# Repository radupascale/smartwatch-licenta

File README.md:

# Intro

This repository contains all the files necessary to build the smartwatch I developed for my thesis at the Computer Science Faculty of UPB.
I plan to add step-by-step building instructions in the future, but for now I'll leave only an overview of the directory structure.

- board: Schematics and PCB layout
    - fusion: Fusion project archive
    - proto: KiCad prototype project
- CAD
    - 3d-files: .stl files for 3D printing the case
    - components: .STEP files for some components
- src: platform.io project files and deps

# Building

```bash
git clone --recurse-submodules git@github.com:radupascale/smartwatch-licenta.git
```

Afterwards open the `src` directory and build&upload using `platformio` (this project used the VScode extension).

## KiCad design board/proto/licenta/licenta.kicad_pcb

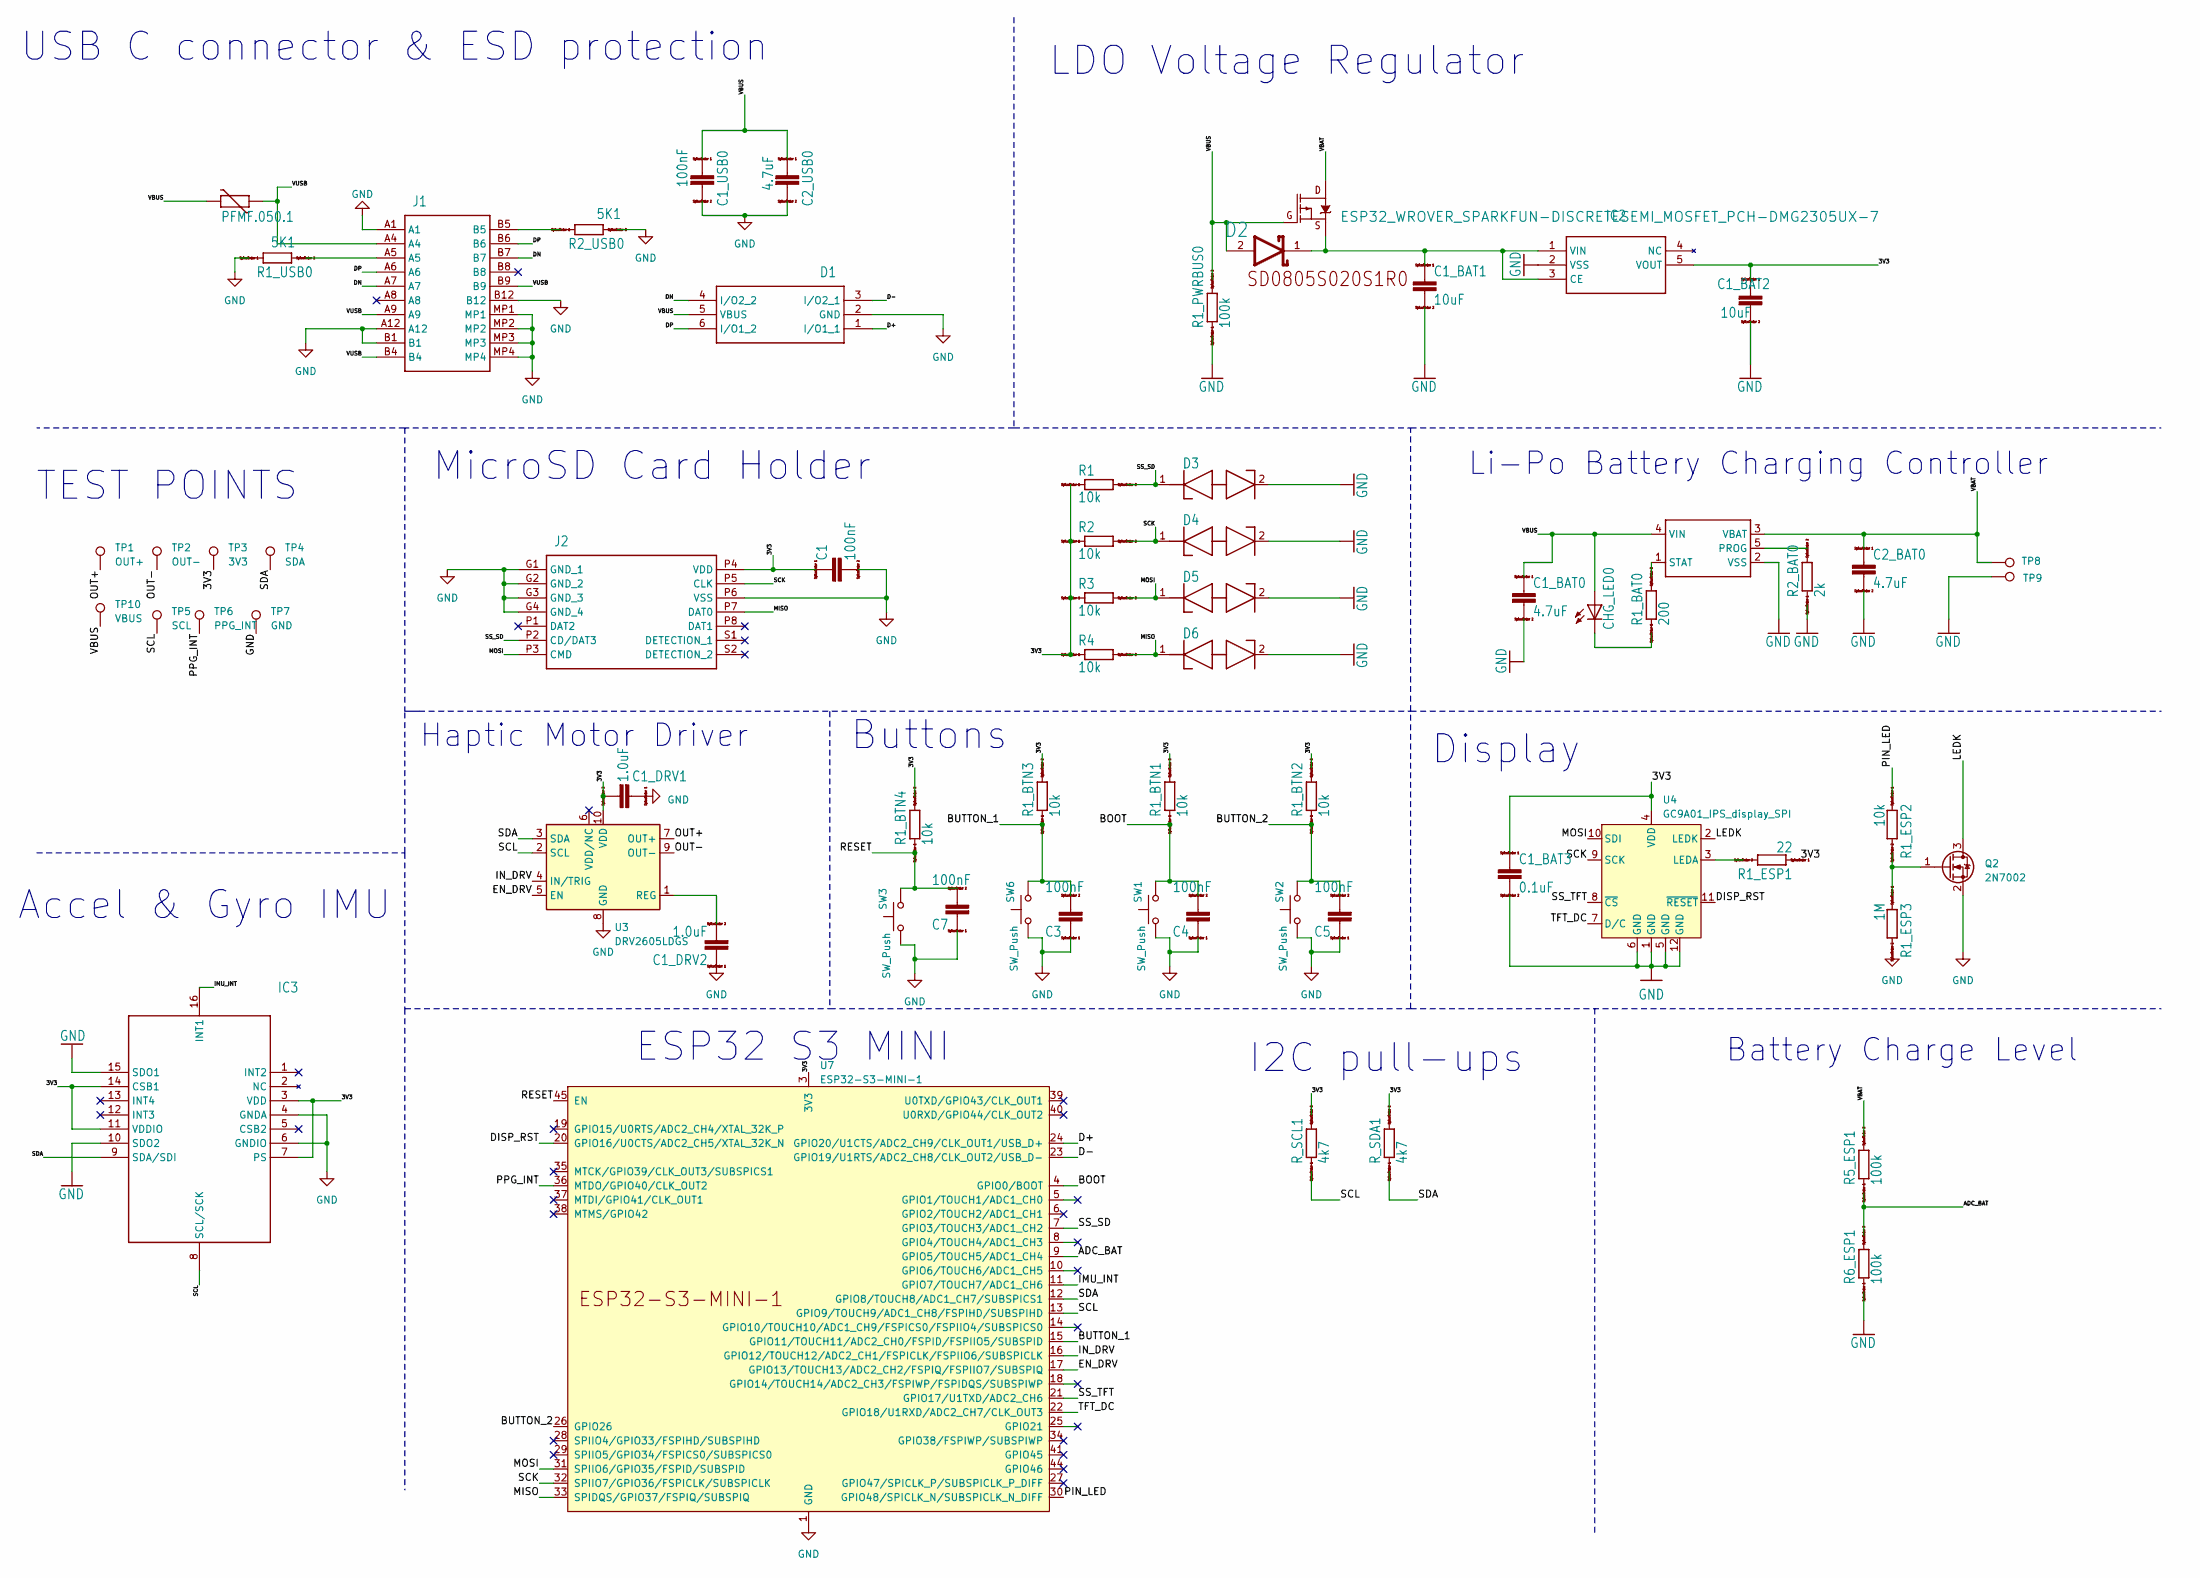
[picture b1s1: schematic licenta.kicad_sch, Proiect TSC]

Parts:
C1, C1_USB0, C3, C4, C5, C7: 100nF; ESP32_WROVER_EAGLE-LTSPICE_C0402
C1_BAT0, C2_BAT0, C2_USB0: 4.7uF; ESP32_WROVER_EAGLE-LTSPICE_C0402
C1_BAT1, C1_BAT2: 10uF; ESP32_WROVER_EAGLE-LTSPICE_C0402
C1_BAT3: 0.1uF; ESP32_WROVER_EAGLE-LTSPICE_C0402
C1_DRV1, C1_DRV2: 1.0uF; ESP32_WROVER_EAGLE-LTSPICE_C0402
CHG_LED0: ESP32_WROVER_ADAFRUIT_LEDCHIP-LED0603; ESP32_WROVER_ADAFRUIT_CHIP-LED0603
D1: SAMACSYS_PARTS_USBLC6-2SC6Y; SAMACSYS_PARTS_SOT95P280X145-6N
D2: ESP32_WROVER_AVX---SD0805S020S1R0_AVX_SD0805S020S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; ESP32_WROVER_AVX---SD0805S020S1R0_AVX_SD0805S020S1R0_0
D3, D4, D5, D6: SAMACSYS_PARTS_PESD3V3S1BLYL; SAMACSYS_PARTS_PESD5V0S1BL315
IC2: XC8107AC20MR-G
IC3: SAMACSYS_PARTS_BMI085
J1: SAMACSYS_PARTS_USB4110-GF-A; SAMACSYS_PARTS_USB4110GFA
J2: SAMACSYS_PARTS_112A-TAAR-R03_ATTEND; SAMACSYS_PARTS_112ATAARR03ATTEND
PFMF.050.1: ESP32_WROVER_VARISTOR_VARISTORCN1812; ESP32_WROVER_VARISTOR_CT_CN1812
Q1: ESP32_WROVER_SPARKFUN-DISCRETESEMI_MOSFET_PCH-DMG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; ESP32_WROVER_SPARKFUN-DISCRETESEMI_SOT23-3
Q2: 2N7002; SOT-23
R1, R1_BTN1, R1_BTN2, R1_BTN3, R1_BTN4, R1_ESP2, R2, R3, R4: 10k; ESP32_WROVER_EAGLE-LTSPICE_R0402
R1_BAT0: 200; ESP32_WROVER_EAGLE-LTSPICE_R0402
R1_ESP1: 22; ESP32_WROVER_EAGLE-LTSPICE_R0402
R1_ESP3: 1M; ESP32_WROVER_EAGLE-LTSPICE_R0402
R1_PWRBUS0, R5_ESP1, R6_ESP1: 100k; ESP32_WROVER_EAGLE-LTSPICE_R0402
R1_USB0, R2_USB0: 5K1; ESP32_WROVER_EAGLE-LTSPICE_R0402
R2_BAT0: 2k; ESP32_WROVER_EAGLE-LTSPICE_R0402
R_SCL1: 4k7; ESP32_WROVER_EAGLE-LTSPICE_R0402
R_SDA1: 4k7; ESP32_WROVER_EAGLE-LTSPICE_R0402
SW1, SW2, SW3, SW6: SW_Push; EVQ-P7K01P
TP1: OUT+; TestPoint_Pad_D2.0mm
TP2: OUT-; TestPoint_Pad_D2.0mm
TP3: 3V3; TestPoint_Pad_D2.0mm
TP4: SDA; TestPoint_Pad_D2.0mm
TP5: SCL; TestPoint_Pad_D2.0mm
TP6: PPG_INT; TestPoint_Pad_D2.0mm
TP7: GND; TestPoint_Pad_D2.0mm
TP8, TP9: TestPoint; TestPoint_Pad_D2.0mm
TP10: VBUS; TestPoint_Pad_1.0x1.0mm
U2: ESP32_WROVER_SPARKFUN-IC-POWER_MCP73831; ESP32_WROVER_SPARKFUN-IC-POWER_SOT23-5
U3: DRV2605LDGS; VSSOP-10_3x3mm_P0.5mm
U4: GC9A01_IPS_display_SPI; GC9A01_IPS_display
U7: ESP32-S3-MINI-1

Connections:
/3V3: C1.1, C1_BAT2.1, C1_BAT3.1, C1_DRV1.2, IC2.5 (VOUT), IC3.3 (VDD), IC3.7 (PS), IC3.11 (VDDIO), IC3.14 (CSB1), J2.P4 (VDD), R1.1, R1_BTN1.2, R1_BTN2.2, R1_BTN3.2, R1_BTN4.2, R1_ESP1.1, R2.1, R3.1, R4.1, R_SCL1.2, R_SDA1.2, TP3.1, U3.10 (VDD), U4.4 (VDD), U7.3 (3V3)
/ADC_BAT: R5_ESP1.1, R6_ESP1.2, U7.9 (GPIO5/TOUCH5/ADC1_CH4)
/BOOT: C4.2, R1_BTN1.1, SW1.2, U7.4 (GPIO0/BOOT)
/BUTTON_1: C3.2, R1_BTN3.1, SW6.2, U7.15 (GPIO11/TOUCH11/ADC2_CH0/FSPID/FSPIIO5/S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)
/BUTTON_2: C5.2, R1_BTN2.1, SW2.2, U7.26 (GPIO26)
/D+: D1.1 (I/O1_1), U7.24 (GPIO20/U1CTS/ADC2_CH9/CLK_OUT1/USB_D+)
/D-: D1.3 (I/O2_1), U7.23 (GPIO19/U1RTS/ADC2_CH8/CLK_OUT2/USB_D-)
/DISP_RST: U4.11 (~RESET), U7.20 (GPIO16/U0CTS/ADC2_CH5/XTAL_32K_N)
/DN: D1.4 (I/O2_2), J1.A7, J1.B7
/DP: D1.6 (I/O1_2), J1.A6, J1.B6
/EN_DRV: U3.5 (EN), U7.17 (GPIO13/TOUCH13/ADC2_CH2/FSPIQ/FSPIIO7/S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)
/IMU_INT: IC3.16 (INT1), U7.11 (GPIO7/TOUCH7/ADC1_CH6)
/IN_DRV: U3.4 (IN/TRIG), U7.16 (GPIO12/TOUCH12/ADC2_CH1/FSPICLK/FSPIIO6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)
/LEDK: Q2.3 (D), U4.2 (LEDK)
/MISO: D6.1 (K1), J2.P7 (DAT0), R4.2, U7.33 (SPIDQS/GPIO37/FSPIQ/SUBSPIQ)
/MOSI: D5.1 (K1), J2.P3 (CMD), R3.2, U4.10 (SDI), U7.31 (SPIIO6/GPIO35/FSPID/SUBSPID)
/OUT+: TP1.1, U3.7 (OUT+)
/OUT-: TP2.1, U3.9 (OUT-)
/PIN_LED: R1_ESP2.1, U7.30 (GPIO48/SPICLK_N/SUBSPICLK_N_DIFF)
/PPG_INT: TP6.1, U7.36 (MTDO/GPIO40/CLK_OUT2)
/RESET: C7.2, R1_BTN4.1, SW3.2, U7.45 (EN)
/SCK: D4.1 (K1), J2.P5 (CLK), R2.2, U4.9 (SCK), U7.32 (SPIIO7/GPIO36/FSPICLK/SUBSPICLK)
/SCL: IC3.8 (SCL/SCK), R_SCL1.1, TP5.1, U3.2 (SCL), U7.13 (GPIO9/TOUCH9/ADC1_CH8/FSPIHD/SUBSPIHD)
/SDA: IC3.9 (SDA/SDI), R_SDA1.1, TP4.1, U3.3 (SDA), U7.12 (GPIO8/TOUCH8/ADC1_CH7/SUBSPICS1)
/SS_SD: D3.1 (K1), J2.P2 (CD/DAT3), R1.2, U7.7 (GPIO3/TOUCH3/ADC1_CH2)
/SS_TFT: U4.8 (~CS), U7.21 (GPIO17/U1TXD/ADC2_CH6)
/TFT_DC: U4.7 (D/C), U7.22 (GPIO18/U1RXD/ADC2_CH7/CLK_OUT3)
/VBAT: C2_BAT0.1, Q1.3 (D), R5_ESP1.2, TP8.1, U2.3 (VBAT)
/VBUS: C1_BAT0.1, C1_USB0.1, C2_USB0.1, CHG_LED0.A, D1.5 (VBUS), D2.2 (ANODE), PFMF.050.1.2, Q1.1 (G), R1_PWRBUS0.2, TP10.1, U2.4 (VIN)
/VUSB: J1.A4, J1.A9, J1.B4, J1.B9, PFMF.050.1.1
GND: C1.2, C1_BAT0.2, C1_BAT1.2, C1_BAT2.2, C1_BAT3.2, C1_DRV1.1, C1_DRV2.1, C1_USB0.2, C2_BAT0.2, C2_USB0.2, C3.1, C4.1, C5.1, C7.1, D1.2 (GND), D3.2 (K2), D4.2 (K2), D5.2 (K2), D6.2 (K2), IC2.2 (VSS), IC3.4 (GNDA), IC3.6 (GNDIO), IC3.10 (SDO2), IC3.15 (SDO1), J1.A1, J1.A12, J1.B1, J1.B12, J1.MP1, J1.MP2, J1.MP3, J1.MP4, J2.G1 (GND_1), J2.G2 (GND_2), J2.G3 (GND_3), J2.G4 (GND_4), J2.P6 (VSS), Q2.2 (S), R1_ESP3.2, R1_PWRBUS0.1, R1_USB0.1, R2_BAT0.1, R2_USB0.2, R6_ESP1.1, SW1.1, SW2.1, SW3.1, SW6.1, TP7.1, TP9.1, U2.2 (VSS), U3.8 (GND), U4.1 (GND), U4.5 (GND), U4.6 (GND), U4.12 (GND), U7.1 (GND), U7.2 (GND), U7.42 (GND), U7.43 (GND), U7.46 (GND), U7.47 (GND), U7.48 (GND), U7.49 (GND), U7.50 (GND), U7.51 (GND), U7.52 (GND), U7.53 (GND), U7.54 (GND), U7.55 (GND), U7.56 (GND), U7.57 (GND), U7.58 (GND), U7.59 (GND), U7.60 (GND), U7.61 (GND), U7.62 (GND), U7.63 (GND), U7.64 (GND), U7.65 (GND)
unnamed: CHG_LED0.C, R1_BAT0.1
unnamed: C1_BAT1.1, D2.1 (CATHODE), IC2.1 (VIN), IC2.3 (CE), Q1.2 (S)
unnamed: J1.A5, R1_USB0.2
unnamed: J1.B5, R2_USB0.1
unnamed: Q2.1 (G), R1_ESP2.2, R1_ESP3.1
unnamed: R2_BAT0.2, U2.5 (PROG)
unnamed: R1_BAT0.2, U2.1 (STAT)
unnamed: C1_DRV2.2, U3.1 (REG)
unnamed: R1_ESP1.2, U4.3 (LEDA)

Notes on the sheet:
TEST POINTS
MicroSD Card Holder
I2C pull-ups
Buttons
USB C connector & ESD protection
Haptic Motor Driver
Li-Po Battery Charging Controller
Accel & Gyro IMU
ESP32 S3 MINI
Display
Battery Charge Level
LDO Voltage Regulator

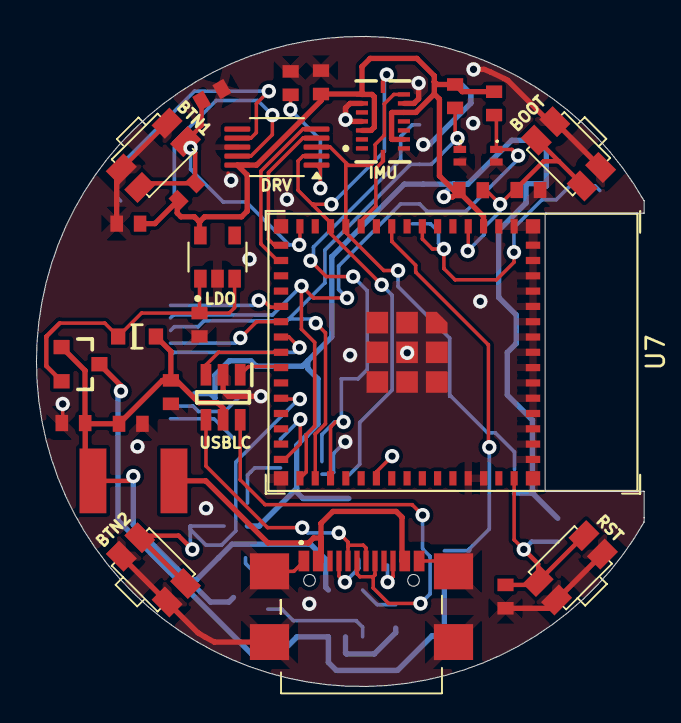
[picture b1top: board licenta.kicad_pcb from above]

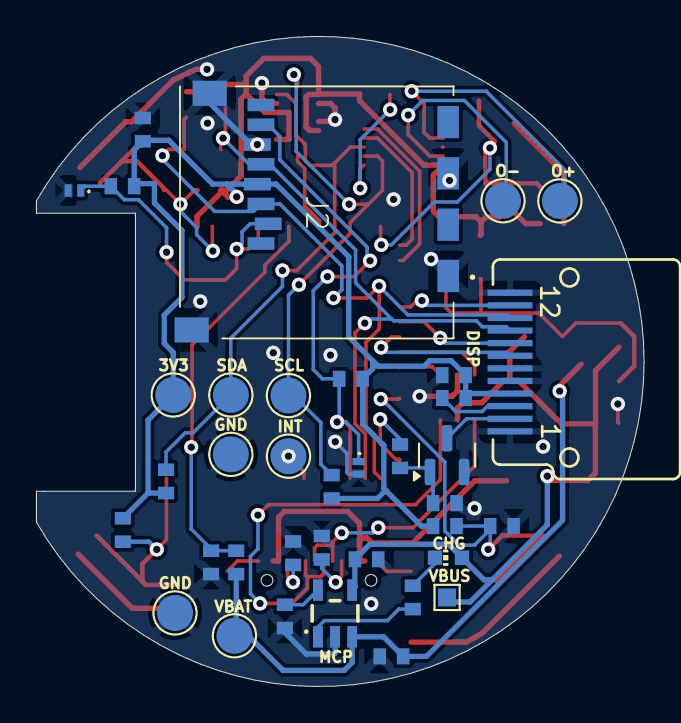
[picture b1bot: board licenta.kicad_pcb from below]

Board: 2 copper layers, 33.8 x 36.1 mm, 66 parts (37 on the bottom side), 40 nets.

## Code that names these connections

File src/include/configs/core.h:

#pragma once
#include "driver/adc.h"
#include "driver/gpio.h"

#define ADC_BAT ADC1_CHANNEL_4
#define CHG_STAT GPIO_NUM_15
#define BUTTON_SELECT GPIO_NUM_0
#define BUTTON_UP GPIO_NUM_11
#define BUTTON_DOWN GPIO_NUM_26
#define RTC_GPIO0 BUTTON_UP

#define BOARD_MISO 37
#define BOARD_SCK 36
#define BOARD_MOSI 35
#define SS_SD 3
#define SS_TFT 17
#define SS_FLASH GPIO_NUM_14
#define EN_DRV GPIO_NUM_13

#define SPI_SPEED (5000000UL)

#define NVS_PEDOMETER_PART "pedometer"
#define DEFAULT_NAMESPACE "default"

#define TWDT_TIMEOUT_MS 3000
#define DEFAULT_CPU_FREQ_MHZ 40
#define ANTENNA_CPU_FREQ_MHZ 80 // wifi and bluetooth only works at this freq
#define INACTIVE_CPU_FREQ_MHZ 20

/* App and GUI notifications */
#define EVENT_NONE (0x00)
#define EVENT_LONG_SELECT (0x01)
#define EVENT_BACK (0x02)
#define EVENT_UP (0x03)
#define EVENT_DOWN (0x04)
#define EVENT_SELECT (0x05)

void os_init(void *pvParam);
void os_gui(void *pvParam);
void os_resumer(void *pvParam);

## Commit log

2023-11-07 init: Test esp32 and gc9a01 TFT display
2023-11-13 Add schematics and rearange files
2023-11-13 Move readme to root directory
2023-11-14 Update schematics w/o PPG
2023-11-18 Finish schematic draft
    Add pin headers for PPG and use 1 pin for reading 3 different buttons
    using the ADC. There's not enough space left for the haptic motor
    driver.
2023-11-18 Add draft schematics pdf
2023-11-21 Add ESP32 S3 mini to schematic
2023-11-22 repo: Remove zone:identifier files
2023-11-22 repo: Remove more zone:identifier files
2023-11-22 repo: Remove even more zone:identifier files
2023-11-22 repo: Update .gitignore
2023-11-23 board: Modify schematic to use ESP32 S3
    Connect the haptic motor driver to the uC, add labels to pinheaders for A1027
    and connect the buttons to different pins.
    Delete ESP32 C3 mini from schematic.
2023-11-23 board: Rearrange directory to separate external libs
2023-11-23 board: Add PCB draft
2023-11-25 Add fusion sketch
2023-12-04 Add test point footprints
2023-12-04 Add display CAD
2023-12-04 Update schematics
    Delete unused components such as LTR and voltage supervisor.
    Replace pinheaders with test pads
2023-12-04 Prototype first PCB version (unrouted)
2023-12-08 Add DRU and minor pads update
2023-12-11 Add DRC and start routing
2023-12-12 Update components layout and route prototype
    Some pins labels on the ESP32 were also modified(BUT NOT THOROUGHLY CHECKED) in order to simplify routing the PCB.
    In addition, this commit also provides some screenshots used for documentation.
2024-02-25 Add STLs for case prototype
2024-03-04 Cleanup repo
2024-03-04 Update PCB design
    This commit changes the button footprints and modifies the silkscreen
    of the PCB.
2024-03-04 Modify button alignment
2024-03-04 Update project
2024-03-09 Update PCB and schematics
    This commit replaces the LDO and imports new libraries
2024-03-10 Update lib and add 3D models
2024-03-10 Update board and schematic
    This commit adds the following modifications:
    - SDA and SCL pull-ups
    - 100nF debounce capacitors for buttons
    - vias tweaks to not come out of pads
    - connect one button to be used both as BOOT and GPIO
2024-03-10 Add gerber zip files
2024-03-13 Update schematic appearance
2024-04-13 Update platformio deps
2024-04-13 Add basic test modules for display, sd and BMI
2024-04-15 Add GFX to lib
2024-04-15 Add haptic motor and PPG lib and test example
2024-04-22 Add monitor_raw option to platformio.ini
2024-04-22 Add lvgl library to platformio.ini
2024-04-22 Add init functions for bmi, display, ppg and drv
    This commit includes several changes:
    - New source files: bmi.cpp, bmi.h, core.h, display.cpp, display.h, drv.cpp, drv.h, main.cpp, ppg.h.
    - Removed test files: test_bmi.cpp, test_display.cpp, test_drv.ino, test_ppg.cpp.
2024-04-23 Move components to a separate directory
2024-04-23 Simple tasks for testing update&display
2024-04-24 Add CMakeLists.txt for src dir
2024-04-24 Add README with build steps
    platformio.ini has a commented flag which might be useful in the future
    for now, lv_conf.h has to be manually moved to libdeps.
2024-04-29 Add 3d-files for working prototype
2024-04-29 refactor: Move components CAD files to a separate directory
    BREAKING CHANGE: Hardcoded Kicad paths will fail for 3D rendering
2024-05-01 Refactor display component
2024-05-03 Add AceButton libdep
    Library to help with reading events generated by
    the pushdown buttons(long press, short press, double press, etc.)
2024-05-03 Remove BMI-display test code
2024-05-03 Add prebuild action for copying lv_conf.h to libdeps directory
2024-05-03 Implement default watch face
    Dummy values substitute the data which will be updated
    after more functionalities will be added.
    Custom fonts and symbols were used with the source linked
    at the top of each file.
2024-05-04 Remove handle_event virtual function from App class
2024-05-04 feat: Setup wireless connection on boot
2024-05-04 feat: Sync system time using SNTP
2024-05-04 feat: Update watch face UI to display current time and date
2024-05-06 refactor: Settings class no longer inherits App
2024-05-06 refactor: Manage all components in a single class
    In the future, multiple apps will use different components and passing a single pointer is simpler than defining a field for every component that the app uses.
2024-05-06 feat: Add functions to enable/disable display
2024-05-06 feat: Add simple task for processing button events and toggling screen
    Long press SELECT to set BL to OFF
    Double press SELECT to set BL to ON
    Rest of the buttons only print the state and the event in the handler.
2024-05-07 fix: Add missing button pins definitions
2024-05-07 build: Move PPG sensor deps to local library
    The compiler would complain about some invalid expressions in a source file of the library.
    This commit contains the modified file, simplifying the build process.
2024-05-07 chore: Modify flash partition size
    Closes Modify platformio partition table #15
2024-05-07 chore: Create a separate file for private configs
2024-05-07 refactor: Create separate class for IMU
2024-05-07 refactor: Initialize IMU in dev manager
2024-05-08 fix: Skip waiting for real-time on watchface app after MAX_TIME_RETRY
2024-05-08 feat: Simple server for displaying real time accel data
2024-05-08 style: Change main formatting
2024-05-08 fix: Rename conflicting defines
2024-05-08 fix: Add missing MAX_TIME_RETRY define
2024-05-08 feat: Add background image to default watchface
2024-05-13 refactor: Move DRV functions to class
2024-05-13 feat: Initialize DRV inside deviceManager
2024-05-13 feat: Modify main for simple components test
    This commit changes `os_init` to only initialize the deviceManager
    (IMU, Display, Buttons and DRV). No WiFi connection is established.
    After initialization, 4 tasks are created:
    - update the Display
    - check button events
    - read accelerometer data and print to serial monitor
2024-05-13 fix: Add sdkconfig file with FREERTOS_HZ set to 1000
2024-05-24 feat: Add start/stop functions for SNTP and WiFi
2024-05-24 refactor: Rename Settings to BoardSettings
2024-06-01 feat: Script for logging and visualizing accelerometer data
    This commit also features an incomplete pedometer implementation
    in Python
2024-06-01 fix: Update lv_conf_copy.py copy path
2024-06-03 feat: Add tweaked pedometer algorithm library as submodule
2024-06-03 chore: Move headers to include dir
2024-06-03 feat: Move board settings to device manager
2024-06-03 feat: Add button and SPI pins defines
2024-06-03 perf: Modify BMI085 readSensor function to only read acceleromter data
2024-06-03 refactor: Move system time waiting to main.cpp
2024-06-03 fix: Update deviceManager constructor
2024-06-03 feat: Pedometer implementation with non-volatile storage step counting
    This commit adds (among other small changes) a task which uses the C-Step-Counter
    library to perform peak detection on accelerometer data.
    This data is also stored on a separate NVS partition on the ESP32S3 every
    10 steps.
2024-06-05 fix: Configure EN pin of drv2605
2024-06-05 refactor: Change the return types of some functions to esp_err_t
2024-06-05 feat: Add simple SD wrapper class
2024-06-05 test: Add unit tests for SD, DRV, IMU and Display
    To use this you need to run using the pio utilitary.
    No mechanism for separating between normal and test
    build is implemented so you have to comment out app_main
    fro src/main.cpp for this to work.
2024-06-05 chore: Move test defines to configs.h
2024-06-05 chore: Removed unused source file for testing sd
2024-06-05 feat: Guard app_main in main.cpp during testing
    This commits adds a pre script which inserts the UNIT_TEST define
    before building
2024-06-07 feat: Add untested simple flash implementation
2024-06-07 fix: Add missing defines for flash
2024-06-07 fix: Solve SPI deadlock problem
2024-06-07 test: Add flash read/write unit test
2024-06-07 feat: Add battery class for displaying battery charge level
    Battery percentage is displayed using a lookup_table which
    linearly maps the adc value to a %
2024-06-07 test: Add battery adc unit test
2024-06-08 feat: Show battery voltage and % on watchface
    Wifi and battery icons placeholders are removed with this commit
2024-06-08 feat: Deep sleep on boot hold and time kept across soft reboots
    This commit moves some initializations from the os_init function
    to the BoardSettings init function.
    With this, the watch attempts to connect to wifi and configure sntp
    only after a hard reboot (RST pressed).
2024-06-08 chore: Update sdkconfig after esp toolchain upgrade
2024-06-11 fix: Change incorrect battery test
2024-06-11 feat: Update battery lookup table with quadratic
2024-06-11 feat: Add script and data for computing voltage to capacity
2024-06-12 feat: Add script to configure defines for shared SPI bus with SdFat
2024-06-15 feat: Update play function to poll GO function
    Playing an effect can now be done by simply calling drv->play()
2024-06-19 feat: Button input handling and inactivity timer
2024-06-19 feat: Accel ODR and defines
2024-06-19 refactor: Delete logs and useless defines
2024-06-19 feat: Update platformio.ini deps and pre action scripts
2024-06-19 feat: Lower CPU frequency before suspending tasks
2024-06-22 feat: Settings app placeholder and move through menu
    This commit moves the DEEP_SLEEP function to a separate
    app that can be accessed using DOULBE_PRESS or LONG_PRESS
    on the boot button.
2024-06-22 docs: Update readme
2024-06-24 feat: Add GUI for every functionality previously implemented
2024-06-24 refactor: Remove unused defines
2024-06-24 refactor: Remove unused function from main
2024-10-18 refactor: Move KiCad board files to a separate dir
2024-10-18 feat: Add updated schematics pdf and fusion project files
2024-10-18 feat: Update 3D files
2024-10-18 docs: Update README.md
